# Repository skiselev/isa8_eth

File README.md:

# ISA 8-Bit Ethernet Controller
ISA 8-Bit Ethernet Network Interface Controller

## Introduction
ISA 8-Bit Ethernet Controller is an open source network interface controller (NIC) card, designed specifically to be used in computers with 8-bit only ISA (aka XT) bus, such as IBM* PC, IBM* PC XT, various PC/XT compatibles, for example [Micro 8088](https://github.com/skiselev/micro_8088) system. It is based on Realtek RTL8019 ethernet controller and is NE2000-compatible.

## Specifications
* ISA 8-bit interface (62 pin / card edge)
* NE2000 compatible
  * Note: Popular Crynwr NE2000 pocket driver does not support NE2000 in 8-bit slots. Please use the [patched driver](software/driver/) instead
* Supports configuration using switches, jumperless configuration using [RSET8019](software/RSET8019/) utility or PnP
  * Uses DIP switches instead of jumpers for reliability and ease of configuration
* Boot ROM support
  * Socket supports 512 KiB Flash ROM, such as SST/Microchip 39SF040
  * Can be configured in 16 KiB, 32 KiB, 64 KiB, or page mode. In page mode the entire 512 KiB are accessible through a 16 KiB window
  * Also compatible with other DIP 32-pin Flash ROMs, such as 128 KiB 39SF010A, and 256 KiB 39SF020, or similar
  * 40-pin memory extension connector allows connecting up to 4 MiB of memory that can be used in page mode

## Hardware Documentation

### Schematic and PCB Layout

[Schematic - Version 1.0](KiCad/ISA8_Ethernet-Schematic-1.0.pdf)

[PCB Layout - Version 1.0](KiCad/ISA8_Ethernet-Board-1.0.pdf)

### Building Instructions

#### Assemble the PCB

* Clean the PCB with alcohol
* Apply fluid flux to SMD components pads
* Solder U1 RTL8019 IC
* Solder R1 - R7 resistors and RN1 - RN4 resistor arrays
  * Note that RN1 - RN3 are only required if using DIP switches for configuration. They are not required for jumperless configuration
* Solder C1 - C8 ceramic capacitors
* Solder C9 and C10 tantalum capacitors
* Solder Y1 crystal
* Optional: Program U3 EEPROM. Make sure to use unique MAC address
  * Note: EEPROM can be programmed later using [PG8019](software/PG8019/) utility
* Solder U3 EEPROM
* Optional: Solder SW1 - SW4 DIP switches and U2 IC socket
* Solder J1 Ethernet jack with integrated magentics
* Clean the remaining flux with alcohol

#### Program EEPROM

If EEPROM has not been programmed prior to assembly, now it is a good time to do so.
The U3 EEPROM contains the following configuration for the RTL8019AS chip:
* MAC address
* ISA resources for jumperless configuration
  * Base I/O address
  * IRQ number
  * Boot ROM mode, size, and base memory address
* Other ethernet controller confirguration - medium type, full duplex, LEDs function, power management settings
* Product ID (not normally used, although some vendor specific drivers might check for it)
* Plug and Play data
  * Vendor ID, serial number, PnP version, I/O, memory, and IRQ resources

This information can be programmed using [PG8019](software/PG8019/) utility. The 8019AS.CFG file contains the recommended configuration. Make sure to edit it, and update the MAC address and the serial number. Note that the MAC address is given in the Big-endian format (that is the last byte has the least significant value), while the serial number is given in Little-endian format (that is the first byte has the least significant value). 

A few notes about using PG8019:
* Make sure that your system has 0x300-0x31F I/O addresses available regardless of the Ethernet controller addresses specified in 8019AS.CFG. Note that XT-IDE and XT-CF-Lite frequently use this I/O range. In case you have such a card, you can either temporarily remove it from your system, boot and run PG8019 from a floppy disk, or switch your XT-IDE or XT-CF-Lite to a different address. In the latter case you'll need to update the XT IDE BIOS configuration
* Make sure that your system boots in real mode (no EMM386), or anything else that might interfer with the card. Ideally boot your system without any drivers loaded at all, for example, in later MS-DOS versions it is possible to bypass CONFIG.SYS and AUTOEXEC.BAT by hitting F5 key at the boot time
* After EEPROM has been programmed successfully, the PG8019 utility will print the MAC address, also, it will automatically increment the MAC address and the serial number in 8019AS.CFG, which is useful when programming multiple cards

[Openmoko Inc.](https://github.com/skiselev/openmoko-usb-oui) has generously allocated [00-1F-11-02-60-00 - 00-1F-11-02-7F-FF](https://github.com/skiselev/openmoko-usb-oui/blob/master/ieee_oui.psv) MAC addresses range for ISA 8-Bit Ethernet controller project. You can use MAC addresses from this range for your build, as long as you are using this design. Please apply for a different range if you're redesigning the board or re-using this Ethernet controller design in your own project. I ask you not to use 00-1F-11-02-60-00 - 00-1F-11-02-63-FF range (first 1024 addresses). I am using this range for the cards that I build.

#### Test Ethernet Controller

* Connect Ethernet cable. Make sure that the green "Link" LED lights up
* Use mTCP to test the controller
  * DHCP to obtain IP address
  * FTP or HTGET to download a file

### Switches and Connectors

#### SW1 - CONFIG
This switch block sets the configuration mode

Configuration Mode    | Switch Position
--------------------- | ------------------------
Jumperless / RSET8019 | SW1.1 = OFF, SW1.2 = OFF
Switches              | SW1.1 = ON, SW1.2 = OFF
PnP                   | SW1.1 = OFF, SW1.2 = ON

#### SW2 - IRQ
This switch block, when the card is in the **Switches** configuration mode, sets the Ethernet controller IRQ

IRQ                             | Switch Position
------------------------------- | ------------------------
IRQ2 (on PC/XT) or IRQ9 (on AT) | SW2.1 = OFF, SW2.2 = OFF
IRQ3                            | SW2.1 = ON, SW2.2 = OFF
IRQ4                            | SW2.1 = OFF, SW2.2 = ON
IRQ5                            | SW2.1 = ON, SW2.2 = ON

#### SW3 - IO_ADDR
This switch block, when the card is in the **Switches** configuration mode, sets the Ethernet controller I/O address

I/O Address | SW3.1 | SW3.2 | SW3.3 | SW3.4
----------- | ----- | ----- | ------| -----
0x200       | OFF   | OFF   | ON    | OFF
0x220       | ON    | OFF   | ON    | OFF
0x240       | OFF   | ON    | ON    | OFF
0x260       | ON    | ON    | ON    | OFF
0x280       | OFF   | OFF   | ON    | ON
0x2A0       | ON    | OFF   | ON    | ON
0x2C0       | OFF   | ON    | ON    | ON
0x2E0       | ON    | ON    | ON    | ON
0x300       | OFF   | OFF   | OFF   | OFF
0x320       | ON    | OFF   | OFF   | OFF
0x340       | OFF   | ON    | OFF   | OFF
0x360       | ON    | ON    | OFF   | OFF
0x380       | OFF   | OFF   | OFF   | ON
0x3A0       | ON    | OFF   | OFF   | ON
0x3C0       | OFF   | ON    | OFF   | ON
0x3E0       | ON    | ON    | OFF   | ON

#### SW4 - ROM_ADDR
This switch block, when the card is in the **Switches** configuration mode, sets the Ethernet controller boot ROM address and size

ROM Address  | ROM Size           | SW4.1 | SW4.2 | SW4.3 | SW4.4 | SW4.5
------------ | ------------------ | ----- | ------| ----- | ----- | -----
ROM Disabled | Not applicable     | *     | *     | *     | OFF   | OFF
0xC0000      | 16 KiB             | OFF   | OFF   | OFF   | OFF   | ON
0xC4000      | 16 KiB             | ON    | OFF   | OFF   | OFF   | ON
0xC8000      | 16 KiB             | OFF   | ON    | OFF   | OFF   | ON
0xCC000      | 16 KiB             | ON    | ON    | OFF   | OFF   | ON
0xD0000      | 16 KiB             | OFF   | OFF   | ON    | OFF   | ON
0xD4000      | 16 KiB             | ON    | OFF   | ON    | OFF   | ON
0xD8000      | 16 KiB             | OFF   | ON    | ON    | OFF   | ON
0xDC000      | 16 KiB             | ON    | ON    | ON    | OFF   | ON
0xC0000      | 32 KiB             | OFF   | OFF   | OFF   | ON    | OFF
0xC8000      | 32 KiB             | ON    | OFF   | OFF   | ON    | OFF
0xD0000      | 32 KiB             | OFF   | ON    | OFF   | ON    | OFF
0xD8000      | 32 KiB             | ON    | ON    | OFF   | ON    | OFF
0xC0000      | 64 KiB             | OFF   | OFF   | ON    | ON    | OFF
0xD0000      | 64 KiB             | ON    | OFF   | ON    | ON    | OFF
0xC0000      | 16 KiB / Page mode | OFF   | OFF   | OFF   | ON    | ON
0xC4000      | 16 KiB / Page mode | ON    | OFF   | OFF   | ON    | ON
0xC8000      | 16 KiB / Page mode | OFF   | ON    | OFF   | ON    | ON
0xCC000      | 16 KiB / Page mode | ON    | ON    | OFF   | ON    | ON
0xD0000      | 16 KiB / Page mode | OFF   | OFF   | ON    | ON    | ON
0xD4000      | 16 KiB / Page mode | ON    | OFF   | ON    | ON    | ON
0xD8000      | 16 KiB / Page mode | OFF   | ON    | ON    | ON    | ON
0xDC000      | 16 KiB / Page mode | ON    | ON    | ON    | ON    | ON

#### J1 - Ethernet Connector

#### J2 - MEM_EXT
This connector can be used to add up to 4 MiB of optional memory (ROM or RAM).
The memory, if larger than 64 KiB, can be accessed using the page mode.

Pin | Description   | Pin | Description
--- | ------------- | --- | -----------
1   | 5V            | 2   | 5V
3   | No connection | 4   | A21
5   | No connection | 6   | A20
7   | No connection | 8   | A19
9   | A18           | 10  | /MEMW
11  | A16           | 12  | A17
13  | A15           | 14  | A14
15  | A12           | 16  | A13
17  | A7            | 18  | A8
19  | A6            | 20  | A9
21  | A5            | 22  | A11
23  | A4            | 24  | /MEMR
25  | A3            | 26  | A10
27  | A2            | 28  | /CS
29  | A1            | 30  | D7
31  | A0            | 32  | D6
33  | D0            | 34  | D5
35  | D1            | 36  | D4
37  | D2            | 38  | D3
39  | GND           | 40  | GND

### Bill of Materials - Version 1.0

[ISA 8-bit Ethernet project on Mouser.com](https://www.mouser.com/ProjectManager/ProjectDetail.aspx?AccessID=6373f65c4a) - View and order all components except of the PCB and the Realtek RTL8019 IC.

[ISA 8-bit Ethernet project on OSH Park](https://oshpark.com/shared_projects/OBud8i6u) - View and order the PCB.

Component type     | Reference | Description                           | Quantity | Possible sources and notes 
------------------ | --------- | ------------------------------------- | -------- | --------------------------
PCB                |           | ISA 8-bit Ethernet PCB - Version 1.0  | 1        | Buy from my Tindie store: [ISA 8-bit Ethernet PCB, and optionally a preprogrammed EEPROM](https://www.tindie.com/products/weird/isa8-eth-pcb), or order from a PCB manufacturer of your choice using provided Gerber or KiCad files
Integrated Circuit | U1        | Realtek RTL8019AS Ethernet Controller | 1        | Authorized Realtek distributors or eBay
Integrated Circuit | U2        | SST39SF040 - 512 KiB Flash ROM, 32 pin DIP  | 1  | Optional - Boot ROM. Mouser [804-39SF0407CPHE](https://www.mouser.com/ProductDetail/804-39SF0407CPHE)
Integrated Circuit | U3        | 93C46 - 1 Kbit EEPROM, 4 pin SOIC     | 1        | Mouser [511-M93C46-WMN6TP](https://www.mouser.com/ProductDetail/511-M93C46-WMN6TP)
Quartz Crystal     | Y1        | 20 MHz, 18pF, HC-49U                  | 1        | Mouser [774-ATS200C](https://www.mouser.com/ProductDetail/774-ATS200C)
Ethernet Jack      | J1        | Amphenol RJMG1BD3B8K1ANR - Ethernet jack with magnetics | 1 | Mouser [523-RJMG1BD3B8K1ANR](https://www.mouser.com/ProductDetail/523-RJMG1BD3B8K1ANR)
DIP Switch         | SW1, SW2  | DIP switch, 2 position, SPST          | 2        | Mouser [774-2102MS](https://www.mouser.com/ProductDetail/774-2102MS)
DIP Switch         | SW3       | DIP switch, 4 position, SPST          | 1        | Mouser [774-2104MS](https://www.mouser.com/ProductDetail/774-2104MS)
DIP Switch         | SW4       | DIP switch, 5 position, SPST          | 1        | Mouser [774-2105MS](https://www.mouser.com/ProductDetail/774-2105MS)
Capacitor          | C1, C2    | 10pF MLCC Capacitor, 0603 SMT         | 2        | Mouser [77-VJ0603A100JXACBC](https://www.mouser.com/ProductDetail/77-VJ0603A100JXACBC)
Capacitor          | C3, C4    | 0.01uF MLCC Capacitor, 0603 SMT       | 2        | Mouser [77-VJ0603Y103JXACBC](https://www.mouser.com/ProductDetail/77-VJ0603Y103JXACBC)
Capacitor          | C5 - C8   | 0.1uF MLCC Capacitor, 0603 SMT        | 4        | Mouser [77-VJ0603Y104JXJPBC](https://www.mouser.com/ProductDetail/77-VJ0603Y104JXJPBC)
Capacitor          | C9, C10   | 22uF Tantalum Capacitor, 1210 SMT     | 2        | Mouser [581-TAJB226K016TNJ](https://www.mouser.com/ProductDetail/581-TAJB226K016TNJ)
Resistor           | R1        | 200 Ohm Resistor, 0603 SMT            | 1        | Mouser [603-RC0603FR-13200RL](https://www.mouser.com/ProductDetail/603-RC0603FR-13200RL)
Resistor           | R2, R3    | 470 Ohm Resistor, 0603 SMT            | 2        | Mouser [603-RC0603FR-13470RL](https://www.mouser.com/ProductDetail/603-RC0603FR-13470RL)
Resistor           | R6        | 27 kOhm Resistor, 0603 SMT            | 1        | Mouser [603-RC0603FR-1327KL](https://www.mouser.com/ProductDetail/603-RC0603FR-1327KL)
Resistor           | R7        | 1 MOhm Resistor, 0603 SMT             | 1        | Mouser [603-RC0603FR-131ML](https://www.mouser.com/ProductDetail/603-RC0603FR-131ML)
Resistor Array     | RN1 - RN4 | 10 kOhm x 4 Resistor Array, 0603 SMT  | 4        | Mouser [667-EXB-38V103JV](https://www.mouser.com/ProductDetail/667-EXB-38V103JV)
IC Socket          | U2        | 32 pin DIP                            | 1        | Mouser [517-4832-6000-CP](https://www.mouser.com/ProductDetail/517-4832-6000-CP)

## Reference Information

### Realtek RTL8019AS EEPROM Content

The Realtek RTL8019AS uses 93C46 - 1Kbit / 128 bytes EEPROM to store the configuration. The EEPROM is accessed using 16-bit word mode, with data being stored in Big-endian format. This means that the bytes should be swapped when the EEPROM content is accessed on an x86 system.

Address      | Size | Content                                | Default Configuration for ISA 8-Bit Ethernet
-------------|------|----------------------------------------|---------------------------------------------
0x00 - 0x03  | 4    | CONFIG1, CONFIG2, CONFIG3, CONFIG4     |
0x00         | 1    | CONFIG1                                | 0x07
0x01         | 1    | CONFIG2                                | 0x00
0x02         | 1    | CONFIG3                                | 0xD0
0x03         | 1    | CONFIG4                                | 0x01
0x04 - 0x09  | 6    | Ethernet ID (MAC Address)              | 0x00 0x1F 0x11 0x02 0x70 0x00
0x0A - 0x11  | 8    | Product ID                             | 0x49 0x53 0x41 0x38 0x45 0x54 0x48 0x20
0x12 - 0x1A  | 9    | PnP header                             | 
0x12 - 0x15  | 4    | Vendor ID (0-3)                        |  
0x12 - 0x13  | 2    | Vendor ID - compressed ASCII (00000=A) | 0x4A 0x8C - 0 10010=R 10100=T 01100=L
0x14 - 0x15  | 2    | Vendor ID - product number             | 0x80 0x19 - 8019
0x16 - 0x19  | 4    | Serial Number (0-3)                    | 0x00 0x10 0x00 0x00
0x1A         | 1    | Checksum                               | ?
0x1B - 0x7F  | 101  | PnP Resource Data                      | 
0x1B - 0x1D  | 3    | PnP Version Number                     |
0x1B         | 1    | Item byte                              | 0x0A
0x1C         | 1    | PnP Version                            | 0x10
0x1D         | 1    | Vendor Version                         | 0x10
0x1E - 0x3B  | 37   | ANSI Identifier String                 | 
0x1E         | 1    | Item byte                              | 0x82
0x1F         | 1    | Length, bits 7-0                       | 0x24
0x20         | 1    | Length, bits 15-8                      | 0x00
0x21 - 0x44  | 36   | Identifier String                      | "ISA 8-Bit Plug & Play Ethernet Card", 0x00
0x45 - 0x4B  | 7    | Logical Device ID                      |
0x45         | 1    | Item byte                              | 0x16
0x46 - 0x49  | 4    | Logical Device ID 0-3                  | 0x00 0x00 0x80 0x19
0x4A         | 1    | Flag 0                                 | 0x02 (Boot ROM disabled) or 0x03 (Boot ROM enabled)
0x4B         | 1    | Flag 1                                 | 0x00
0x4C - 0x50  | 5    | Compatible Device ID (NE2000 compatible) |
0x4C         | 1    | Item byte                              | 0x1C
0x4D - 0x50  | 4    | Compatible ID                          | 0x41 0xD0 0x80 0xD6
0x51 - 0x58  | 8    | I/O Format                             |
0x51         | 1    | Item byte                              | 0x47
0x52         | 1    | I/O Information                        | 0x00
0x53         | 1    | Minimal I/O base, bits 7-0             | 0x20
0x54         | 1    | Minimal I/O base, bits 15-8            | 0x02
0x55         | 1    | Maximal I/O base, bits 7-0             | 0x80
0x56         | 1    | Maximal I/O base, bits 15-8            | 0x03
0x57         | 1    | Base alignment                         | 0x20
0x58         | 1    | Range length                           | 0x20
0x59 - 0x5C  | 4    | IRQ Format                             |
0x59         | 1    | Item byte                              | 0x23 - Small item name = 0x04 (IRQ), Length = 3
0x5A         | 1    | IRQ mask bits 7-0                      | 0x3C - IRQ 0-7 mask - IRQ5, IRQ4, IRQ3, IRQ2
0x5B         | 1    | IRQ mask bits 15-8                     | 0x02 - IRQ 8-15 mask - IRQ9 (note: IRQ9 is the same as IRQ2, others are not available on an 8-bit slot)
0x5C         | 1    | IRQ information                        | 0x01 - High true edge sensitive
0x5D - 0x6A  | 12   | Memory Format (optional)               | 64 KiB Boot ROM (16 KiB Boot ROM)
0x5D         | 1    | Item byte                              | 0x81
0x5E         | 1    | Length, bits 7-0                       | 0x09
0x5F         | 1    | Length, bits 15-8                      | 0x00
0x60         | 1    | Memory information                     | 0x40
0x61         | 1    | Minimal base, bits 15-8                | 0x00
0x62         | 1    | Minimal base, bits 24-16               | 0x0C
0x63         | 1    | Maximal base, bits 7-0                 | 0x00 (0xC0 for 16 KiB)
0x64         | 1    | Maximal base, bits 15-8                | 0x0D
0x65         | 1    | Base alignment, bits 7-0               | 0x00
0x66         | 1    | Base alignment, bits 15-8              | 0x00 (0x40 for 16 KiB)
0x67         | 1    | Range length bits 15-8                 | 0x00 (0x40 for 16 KiB)
0x68         | 1    | Range length bits 24-16                | 0x01 (0x00 for 16 KiB)
0x69 - 0x6A  | 2    | End Tag                                |
0x6B         | 1    | Item byte                              | 0x79
0x6C         | 1    | Checksum of the resource data          | 0x1F
0x6D-0x7F    | ?    | Unused space                           | 0xFF

## Red Tape

### Licensing

ISA 8-bit Ethernet is an open source hardware project certified by [Open Source Hardware Association](https://www.oshwa.org/), certification UID is [US002001](https://certification.oshwa.org/us002001.html). The hardware design itself, including schematic and PCB layout design files are licensed under the strongly-reciprocal variant of [CERN Open Hardware Licence version 2](license-cern_ohl_s_v2.txt). The NE2000 driver code is licensed under [GNU General Public License v2](license-gpl-2.0.txt). Documentation, including this file, is licensed under the [Creative Commons Attribution-ShareAlike 4.0 International License](license-cc-by-sa-4.0.txt).

KiCad symbols and modules used in this project are available in [my KiCad library](https://github.com/skiselev/my_kicad_library) repository

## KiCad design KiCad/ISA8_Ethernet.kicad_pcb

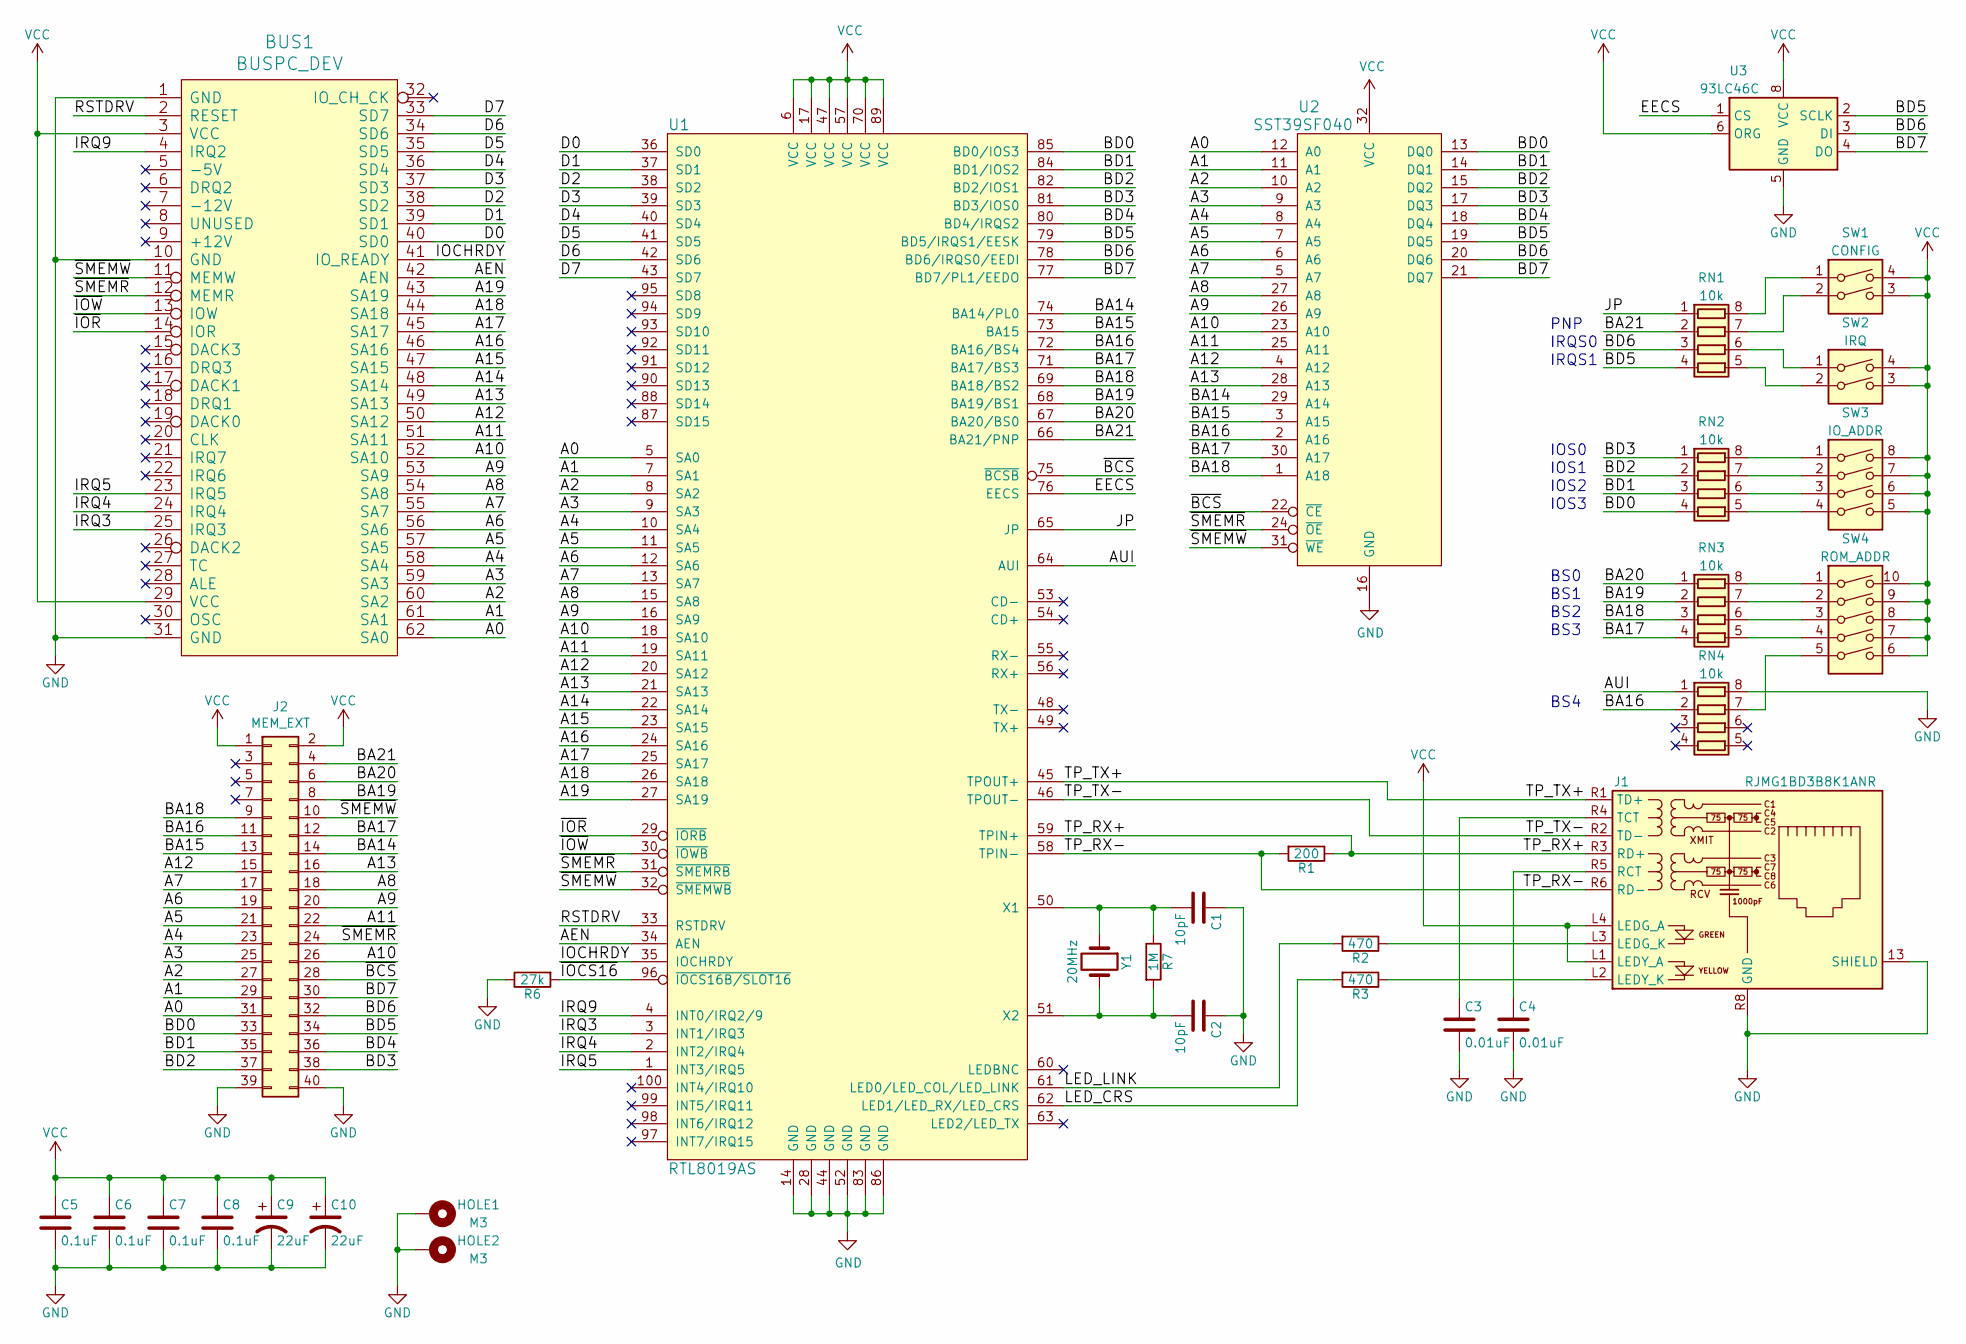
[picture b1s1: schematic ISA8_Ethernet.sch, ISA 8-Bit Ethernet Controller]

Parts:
BUS1: BUSPC_DEV; Conn_Edge_PCB_ISA8
C1, C2: 10pF; C_0603_1608Metric_Pad1.08x0.95mm_HandSolder
C3, C4: 0.01uF; C_0603_1608Metric_Pad1.08x0.95mm_HandSolder
C5, C6, C7, C8: 0.1uF; C_0603_1608Metric_Pad1.08x0.95mm_HandSolder
C9, C10: 22uF; CP_EIA-3528-15_AVX-H_Pad1.50x2.35mm_HandSolder
HOLE1, HOLE2: M3; MountingHole_3.2mm_M3_Pad_Via
J1: RJMG1BD3B8K1ANR; RJ45_Amphenol_RJMG1BD3B8K1ANR
J2: MEM_EXT; Conn_Pin_Header_20x2_2.54mm
R1: 200; R_0603_1608Metric_Pad0.98x0.95mm_HandSolder
R2, R3: 470; R_0603_1608Metric_Pad0.98x0.95mm_HandSolder
R6: 27k; R_0603_1608Metric_Pad0.98x0.95mm_HandSolder
R7: 1M; R_0603_1608Metric_Pad0.98x0.95mm_HandSolder
RN1, RN2, RN3, RN4: 10k; R_Array_Convex_4x0603
SW1: CONFIG; Switch_DIP_2_Positions
SW2: IRQ; Switch_DIP_2_Positions
SW3: IO_ADDR; Switch_DIP_4_Positions
SW4: ROM_ADDR; Switch_DIP_5_Positions
U1: RTL8019AS; IC_PQFP-100_14x20mm_P0.65mm_Hand_Soldering
U2: SST39SF040; Socket_DIP32_600
U3: 93LC46C; SO-8_3.9x4.9mm_P1.27mm
Y1: 20MHz; Crystal_HC-49U_Vert

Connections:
/A0: BUS1.62 (SA0), J2.31, U1.5 (SA0), U2.12 (A0)
/A1: BUS1.61 (SA1), J2.29, U1.7 (SA1), U2.11 (A1)
/A2: BUS1.60 (SA2), J2.27, U1.8 (SA2), U2.10 (A2)
/A3: BUS1.59 (SA3), J2.25, U1.9 (SA3), U2.9 (A3)
/A4: BUS1.58 (SA4), J2.23, U1.10 (SA4), U2.8 (A4)
/A5: BUS1.57 (SA5), J2.21, U1.11 (SA5), U2.7 (A5)
/A6: BUS1.56 (SA6), J2.19, U1.12 (SA6), U2.6 (A6)
/A7: BUS1.55 (SA7), J2.17, U1.13 (SA7), U2.5 (A7)
/A8: BUS1.54 (SA8), J2.18, U1.15 (SA8), U2.27 (A8)
/A9: BUS1.53 (SA9), J2.20, U1.16 (SA9), U2.26 (A9)
/A10: BUS1.52 (SA10), J2.26, U1.18 (SA10), U2.23 (A10)
/A11: BUS1.51 (SA11), J2.22, U1.19 (SA11), U2.25 (A11)
/A12: BUS1.50 (SA12), J2.15, U1.20 (SA12), U2.4 (A12)
/A13: BUS1.49 (SA13), J2.16, U1.21 (SA13), U2.28 (A13)
/A14: BUS1.48 (SA14), U1.22 (SA14)
/A15: BUS1.47 (SA15), U1.23 (SA15)
/A16: BUS1.46 (SA16), U1.24 (SA16)
/A17: BUS1.45 (SA17), U1.25 (SA17)
/A18: BUS1.44 (SA18), U1.26 (SA18)
/A19: BUS1.43 (SA19), U1.27 (SA19)
/AEN: BUS1.42 (AEN), U1.34 (AEN)
/AUI: RN4.1 (R1.1), U1.64 (AUI)
/BA14: J2.14, U1.74 (BA14/PL0), U2.29 (A14)
/BA15: J2.13, U1.73 (BA15), U2.3 (A15)
/BA16: J2.11, RN4.2 (R2.1), U1.72 (BA16/BS4), U2.2 (A16)
/BA17: J2.12, RN3.4 (R4.1), U1.71 (BA17/BS3), U2.30 (A17)
/BA18: J2.9, RN3.3 (R3.1), U1.69 (BA18/BS2), U2.1 (A18)
/BA19: J2.8, RN3.2 (R2.1), U1.68 (BA19/BS1)
/BA20: J2.6, RN3.1 (R1.1), U1.67 (BA20/BS0)
/BA21: J2.4, RN1.2 (R2.1), U1.66 (BA21/PNP)
/BD0: J2.33, RN2.4 (R4.1), U1.85 (BD0/IOS3), U2.13 (DQ0)
/BD1: J2.35, RN2.3 (R3.1), U1.84 (BD1/IOS2), U2.14 (DQ1)
/BD2: J2.37, RN2.2 (R2.1), U1.82 (BD2/IOS1), U2.15 (DQ2)
/BD3: J2.38, RN2.1 (R1.1), U1.81 (BD3/IOS0), U2.17 (DQ3)
/BD4: J2.36, U1.80 (BD4/IRQS2), U2.18 (DQ4)
/BD5: J2.34, RN1.4 (R4.1), U1.79 (BD5/IRQS1/EESK), U2.19 (DQ5), U3.2 (SCLK)
/BD6: J2.32, RN1.3 (R3.1), U1.78 (BD6/IRQS0/EEDI), U2.20 (DQ6), U3.3 (DI)
/BD7: J2.30, U1.77 (BD7/PL1/EEDO), U2.21 (DQ7), U3.4 (DO)
/D0: BUS1.40 (SD0), U1.36 (SD0)
/D1: BUS1.39 (SD1), U1.37 (SD1)
/D2: BUS1.38 (SD2), U1.38 (SD2)
/D3: BUS1.37 (SD3), U1.39 (SD3)
/D4: BUS1.36 (SD4), U1.40 (SD4)
/D5: BUS1.35 (SD5), U1.41 (SD5)
/D6: BUS1.34 (SD6), U1.42 (SD6)
/D7: BUS1.33 (SD7), U1.43 (SD7)
/EECS: U1.76 (EECS), U3.1 (CS)
/IOCHRDY: BUS1.41 (IO_READY), U1.35 (IOCHRDY)
/IRQ3: BUS1.25 (IRQ3), U1.3 (INT1/IRQ3)
/IRQ4: BUS1.24 (IRQ4), U1.2 (INT2/IRQ4)
/IRQ5: BUS1.23 (IRQ5), U1.1 (INT3/IRQ5)
/IRQ9: BUS1.4 (IRQ2), U1.4 (INT0/IRQ2/9)
/JP: RN1.1 (R1.1), U1.65 (JP)
/LED_CRS: R3.2, U1.62 (LED1/LED_RX/LED_CRS)
/LED_LINK: R2.2, U1.61 (LED0/LED_COL/LED_LINK)
/RSTDRV: BUS1.2 (RESET), U1.33 (RSTDRV)
/TP_RX+: J1.R3 (RD+), R1.1, U1.59 (TPIN+)
/TP_RX-: J1.R6 (RD-), R1.2, U1.58 (TPIN-)
/TP_TX+: J1.R1 (TD+), U1.45 (TPOUT+)
/TP_TX-: J1.R2 (TD-), U1.46 (TPOUT-)
/~BCS: J2.28, U1.75 (~BCSB), U2.22 (~CE)
/~IOCS16: R6.2, U1.96 (~IOCS16B/SLOT16)
/~IOR: BUS1.14 (IOR), U1.29 (~IORB)
/~IOW: BUS1.13 (IOW), U1.30 (~IOWB)
/~SMEMR: BUS1.12 (MEMR), J2.24, U1.31 (~SMEMRB), U2.24 (~OE)
/~SMEMW: BUS1.11 (MEMW), J2.10, U1.32 (~SMEMWB), U2.31 (~WE)
GND: BUS1.1 (GND), BUS1.10 (GND), BUS1.31 (GND), C1.1, C2.1, C3.2, C4.2, C5.2, C6.2, C7.2, C8.2, C9.2, C10.2, HOLE1.1, HOLE2.1, J1.13 (SHIELD), J1.R8 (GND), J2.39, J2.40, R6.1, RN4.8 (R1.2), U1.14 (GND), U1.28 (GND), U1.44 (GND), U1.52 (GND), U1.83 (GND), U1.86 (GND), U2.16 (GND), U3.5 (GND)
unnamed: C1.2, R7.1, U1.50 (X1), Y1.1
unnamed: C2.2, R7.2, U1.51 (X2), Y1.2
unnamed: C3.1, J1.R4 (TCT)
unnamed: C4.1, J1.R5 (RCT)
unnamed: J1.L2 (LEDY_K), R3.1
unnamed: J1.L3 (LEDG_K), R2.1
unnamed: RN1.5 (R4.2), SW2.2
unnamed: RN1.6 (R3.2), SW2.1
unnamed: RN1.7 (R2.2), SW1.2
unnamed: RN1.8 (R1.2), SW1.1
unnamed: RN2.5 (R4.2), SW3.4
unnamed: RN2.6 (R3.2), SW3.3
unnamed: RN2.7 (R2.2), SW3.2
unnamed: RN2.8 (R1.2), SW3.1
unnamed: RN3.5 (R4.2), SW4.4
unnamed: RN3.6 (R3.2), SW4.3
unnamed: RN3.7 (R2.2), SW4.2
unnamed: RN3.8 (R1.2), SW4.1
unnamed: RN4.7 (R2.2), SW4.5
VCC: BUS1.3 (VCC), BUS1.29 (VCC), C5.1, C6.1, C7.1, C8.1, C9.1, C10.1, J1.L1 (LEDY_A), J1.L4 (LEDG_A), J2.1, J2.2, SW1.3, SW1.4, SW2.3, SW2.4, SW3.5, SW3.6, SW3.7, SW3.8, SW4.6, SW4.7, SW4.8, SW4.9, SW4.10, U1.6 (VCC), U1.17 (VCC), U1.47 (VCC), U1.57 (VCC), U1.70 (VCC), U1.89 (VCC), U2.32 (VCC), U3.6 (ORG), U3.8 (VCC)

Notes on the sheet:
IOS0
IOS1
IOS2
IOS3
IRQS0
IRQS1
BS4
BS3
BS2
BS1
BS0
PNP

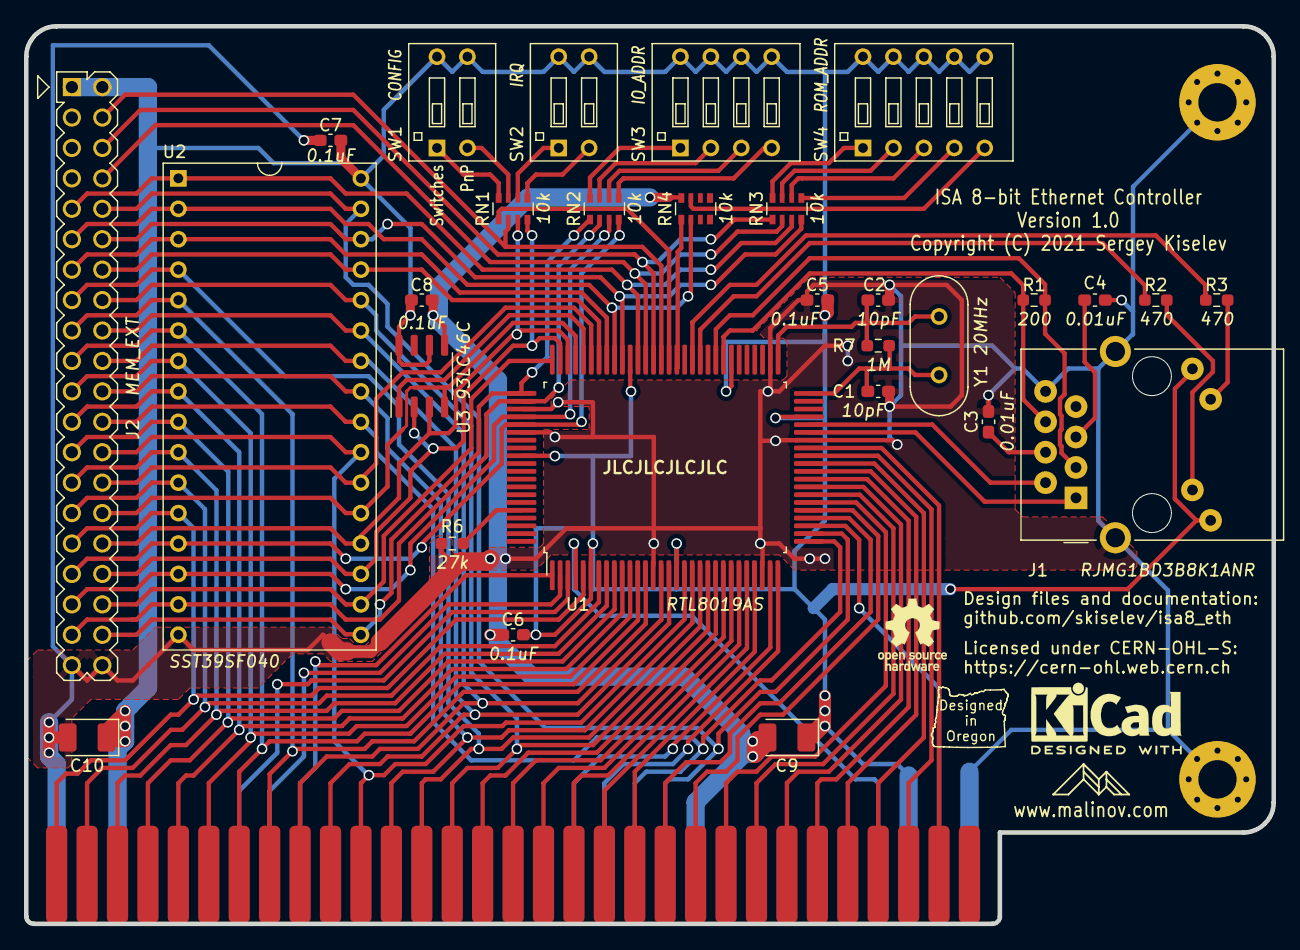
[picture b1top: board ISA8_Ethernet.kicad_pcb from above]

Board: 2 copper layers, 104.1 x 74.9 mm, 32 parts (0 on the bottom side), 87 nets.

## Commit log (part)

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2021-04-23 Upload KiCad files
2021-04-23 Add PDF files
2021-04-23 Add title block
2021-05-20 Update KiCad files
2021-05-20 Add Gerber files
2021-05-20 Add photo of the assembled board
2021-05-20 README: Introduction, Specifications, parts of Hardware Documentation
2021-05-21 README: Add BOM
2021-05-21 README: Update driver license
2021-05-22 README: Typo fix
2021-05-22 README: Add OSH Park link
2021-05-22 README: License facts
2021-05-22 images: Add license facts image
2021-05-22 Add license files
2021-05-22 README: Add link to the KiCad library
2021-05-26 README: Update Open Source Hardware Association UID
2021-10-27 Add 3d printed bracket
2021-10-27 Update Ethernet cutout size and location
2021-11-10 README: Fix typos, add driver link
2021-11-10 Add driver
2021-11-11 README: Add switches
2021-11-12 Add license for the driver
2021-11-12 Add RSET8019 and PG8019, update README accordingly
2021-12-13 README: Add EPROM programming instructions
2021-12-13 Rename vendor provided configuration files, add 8019AS.CFG with the recommended configuration
2021-12-14 README: Add EEPROM data information
2024-10-03 README: Fix C10 and C11 references in BoM

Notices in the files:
README.md:
Licensing:
ISA 8-bit Ethernet is an open source hardware project certified by [Open Source Hardware Association](https://www.oshwa.org/), certification UID is [US002001](https://certification.oshwa.org/us002001.html). The hardware design itself, including schematic and PCB layout design files are licensed under the strongly-reciprocal variant of [CERN Open Hardware Licence version 2](license-cern_ohl_s_v2.txt). The NE2000 driver code is licensed under [GNU General Public License v2](license-gpl-2.0.txt). Documentation, including this file, is licensed under the [Creative Commons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
